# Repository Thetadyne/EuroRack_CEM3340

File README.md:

# SynthMeetupVCO-1
This repository is to hold assets (e.g., design files, code, datasheets) for the first VCO project of the Freeside Atlanta Synth Meetup.

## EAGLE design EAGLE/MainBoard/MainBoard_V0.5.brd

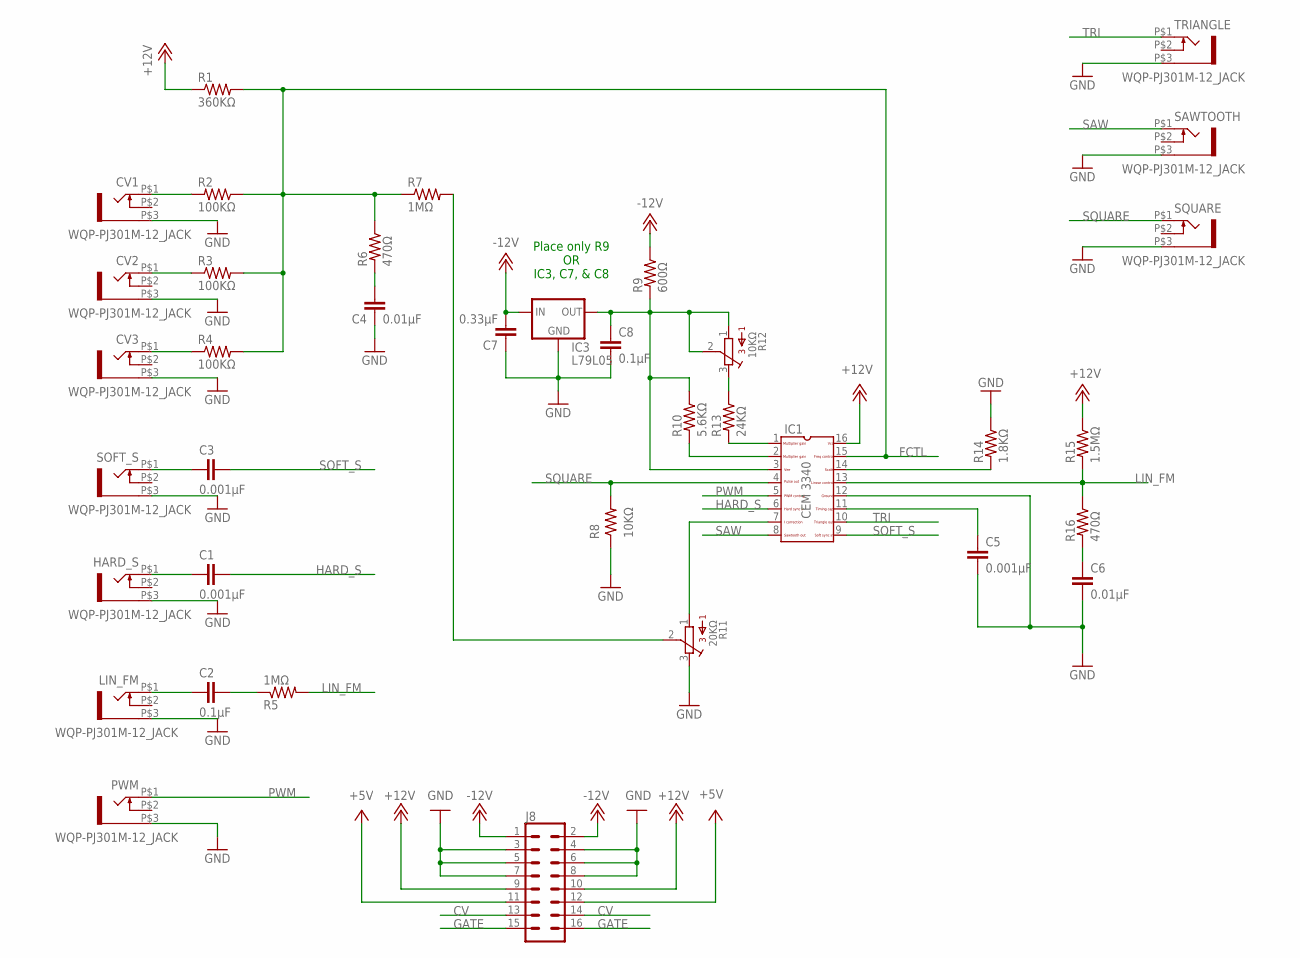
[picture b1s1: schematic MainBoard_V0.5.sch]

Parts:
C1, C3, C5: 0.001μF; C050-025X075
C2, C8: 0.1μF; C050-025X075
C4, C6: 0.01μF; C050-025X075
C7: 0.33μF; C050-025X075
CV1, CV2, CV3: WQP-PJ301M-12_JACK
HARD_S: WQP-PJ301M-12_JACK
IC1: CEM3340; DIL16
IC3: L79L05; TO-92
J8: CONN_08X2_SHROUD; 2X8-SHROUDED_LOCK
LIN_FM: WQP-PJ301M-12_JACK
PWM: WQP-PJ301M-12_JACK
R1: 360KΩ; 0207/10
R2, R3, R4: 100KΩ; 0207/10
R5, R7: 1MΩ; 0207/10
R6, R16: 470Ω; 0207/10
R8: 10KΩ; 0207/10
R9: 600Ω; 0207/10
R10: 5.6KΩ; 0207/10
R11: 20KΩ; 3386W
R12: 10KΩ; 3386W
R13: 24KΩ; 0207/10
R14: 1.8KΩ; 0207/10
R15: 1.5MΩ; 0207/10
SAWTOOTH: WQP-PJ301M-12_JACK
SOFT_S: WQP-PJ301M-12_JACK
SQUARE: WQP-PJ301M-12_JACK
TRIANGLE: WQP-PJ301M-12_JACK

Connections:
+5V: J8.11, J8.12
+12V: IC1.16, J8.9, J8.10, R1.1, R15.1
-12V: C7.2, IC3.2 (IN), J8.1, J8.2, R9.1
CV: J8.13, J8.14
FCTL: IC1.15, R1.2, R2.1, R3.2, R4.2, R6.1, R7.1
GATE: J8.15, J8.16
GND: C4.2, C5.2, C6.2, C7.1, C8.2, CV1.P$3 (1), CV2.P$3 (1), CV3.P$3 (1), HARD_S.P$3 (1), IC1.12, IC3.1 (GND), J8.3, J8.4, J8.5, J8.6, J8.7, J8.8, LIN_FM.P$3 (1), PWM.P$3 (1), R8.1, R11.3, R14.1, SAWTOOTH.P$3 (1), SOFT_S.P$3 (1), SQUARE.P$3 (1), TRIANGLE.P$3 (1)
HARD_S: C1.2, IC1.6
LIN_FM: IC1.13, R5.2, R15.2, R16.1
unnamed: IC1.2, R10.2
unnamed: C4.1, R6.2
unnamed: IC1.14, R14.2
unnamed: C2.1, LIN_FM.P$1 (2)
unnamed: C2.2, R5.1
unnamed: C6.1, R16.2
unnamed: C5.1, IC1.11
unnamed: IC1.1, R13.2
unnamed: R7.2, R11.2
unnamed: R12.3, R13.1
unnamed: IC1.7, R11.1
unnamed: CV1.P$1 (2), R2.2
unnamed: C8.1, IC1.3, IC3.3 (OUT), R9.2, R10.1, R12.1, R12.2
unnamed: C1.1, HARD_S.P$1 (2)
unnamed: CV2.P$1 (2), R3.1
unnamed: CV3.P$1 (2), R4.1
unnamed: C3.2, SOFT_S.P$1 (2)
PWM: IC1.5, PWM.P$1 (2)
SAW: IC1.8, SAWTOOTH.P$1 (2)
SOFT_S: C3.1, IC1.9
SQUARE: IC1.4, R8.2, SQUARE.P$1 (2)
TRI: IC1.10, TRIANGLE.P$1 (2)

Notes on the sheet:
Place only R9 OR IC3, C7, & C8

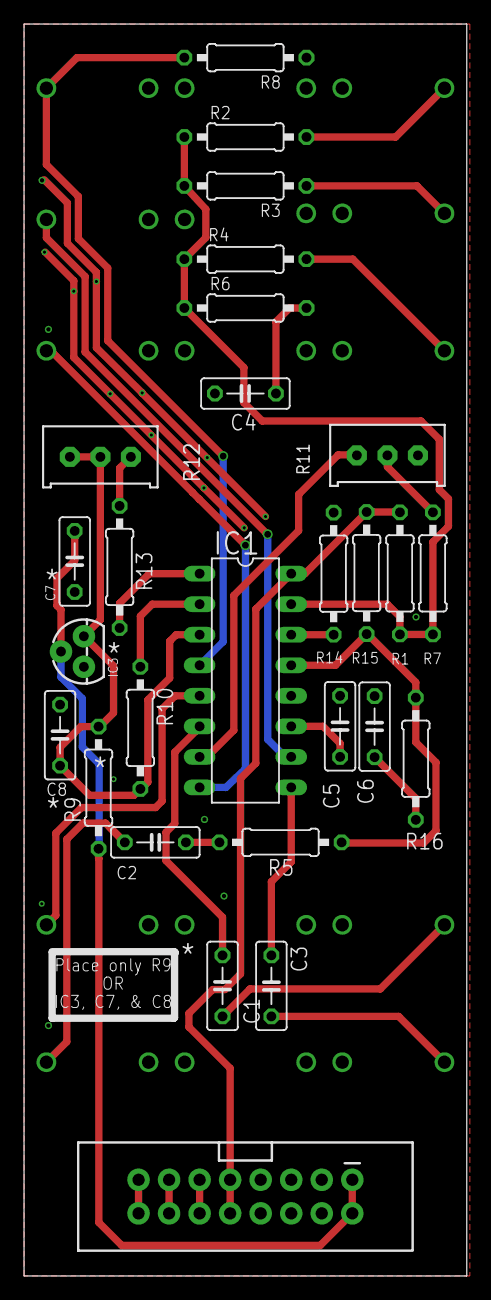
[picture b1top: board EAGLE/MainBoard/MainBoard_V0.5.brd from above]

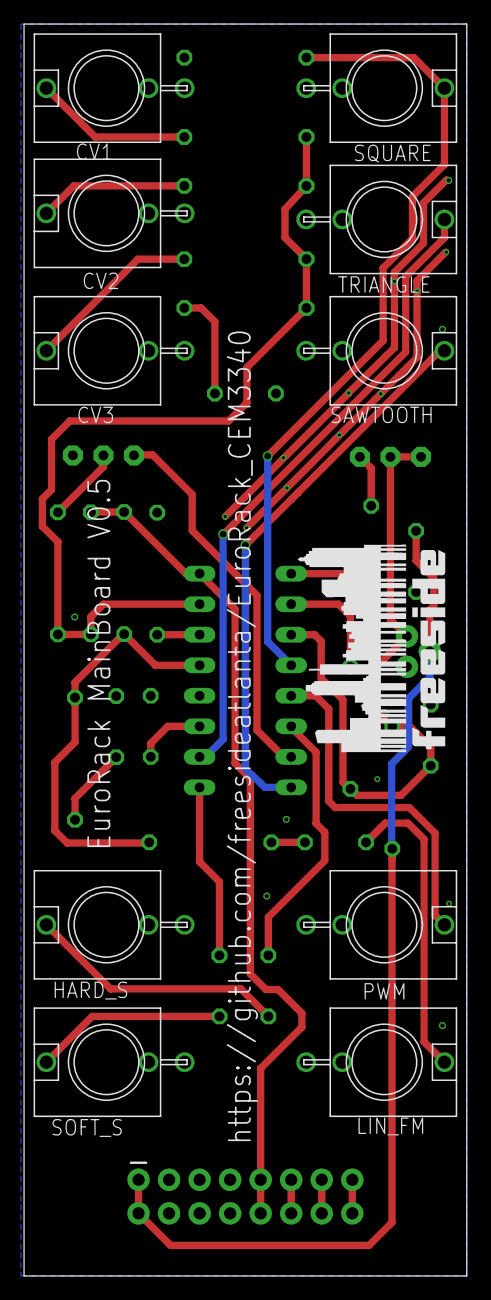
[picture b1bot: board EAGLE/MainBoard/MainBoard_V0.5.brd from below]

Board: 2 copper layers, 36.8 x 104.1 mm, 37 parts (10 on the bottom side), 31 nets.

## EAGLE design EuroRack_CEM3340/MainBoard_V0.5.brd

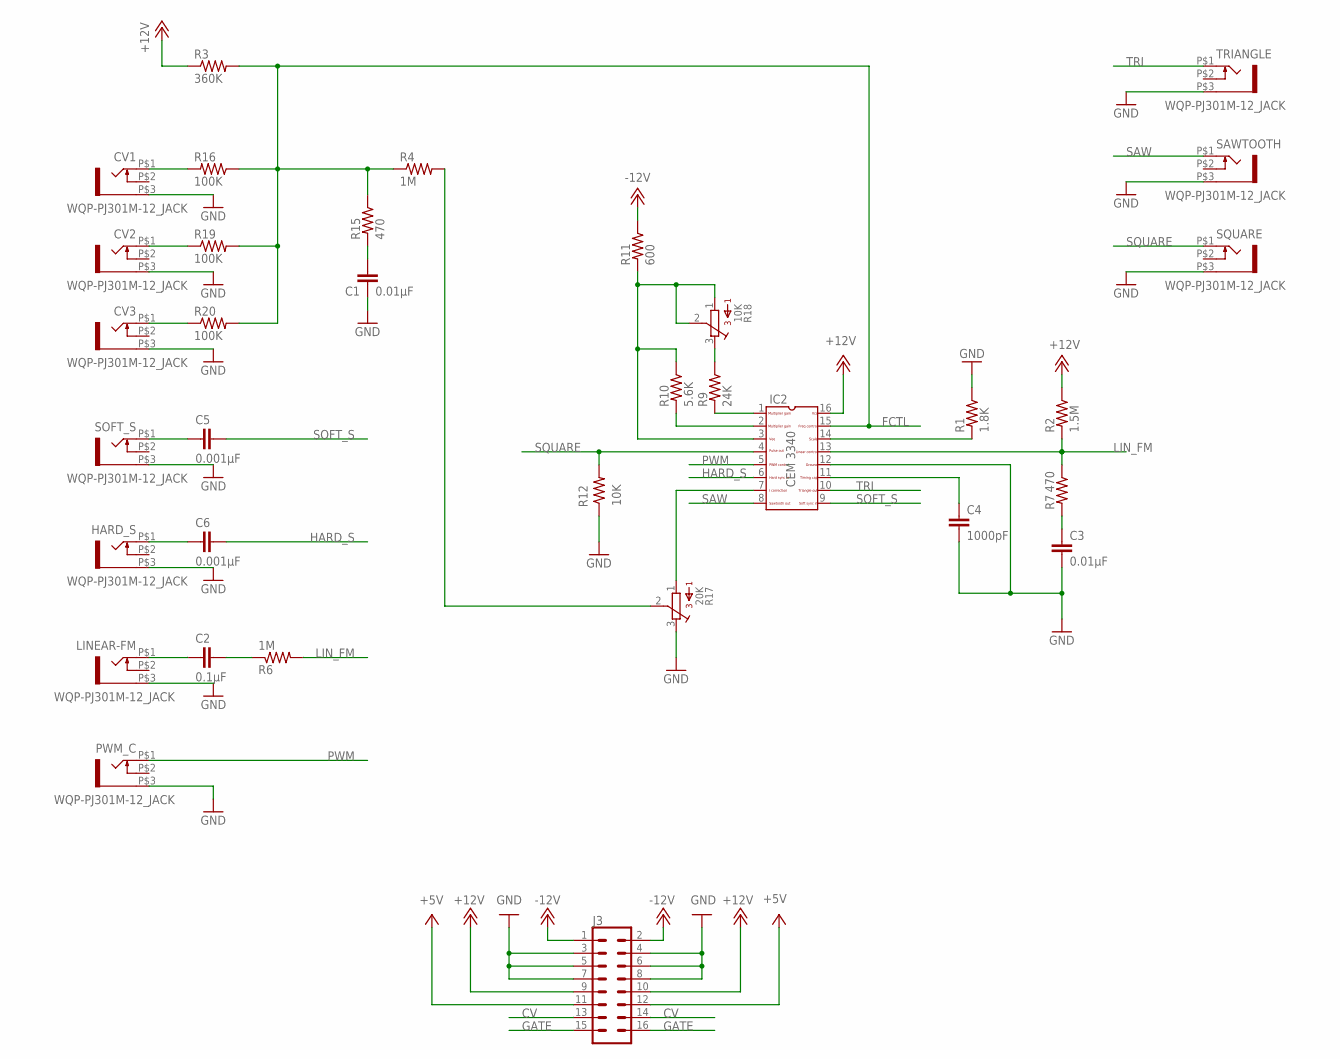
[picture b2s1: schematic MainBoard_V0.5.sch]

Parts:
C1, C3: 0.01μF; C050-025X075
C2: 0.1μF; C050-025X075
C4: 1000pF; C050-025X075
C5, C6: 0.001μF; C050-025X075
CV1, CV2, CV3: WQP-PJ301M-12_JACK
HARD_S: WQP-PJ301M-12_JACK
IC2: CEM3340; DIL16
J3: CONN_08X2_SHROUD; 2X8-SHROUDED_LOCK
LINEAR-FM: WQP-PJ301M-12_JACK
PWM_C: WQP-PJ301M-12_JACK
R1: 1.8K; 0207/10
R2: 1.5M; 0207/10
R3: 360K; 0207/10
R4, R6: 1M; 0207/10
R7, R15: 470; 0207/10
R9: 24K; 0207/10
R10: 5.6K; 0207/10
R11: 600; 0207/10
R12: 10K; 0207/10
R16, R19, R20: 100K; 0207/10
R17: 20K; 3386W
R18: 10K; 3386W
SAWTOOTH: WQP-PJ301M-12_JACK
SOFT_S: WQP-PJ301M-12_JACK
SQUARE: WQP-PJ301M-12_JACK
TRIANGLE: WQP-PJ301M-12_JACK

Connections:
+5V: J3.11, J3.12
+12V: IC2.16, J3.9, J3.10, R2.1, R3.1
-12V: J3.1, J3.2, R11.1
CV: J3.13, J3.14
FCTL: IC2.15, R3.2, R4.1, R15.1, R16.1, R19.2, R20.2
GATE: J3.15, J3.16
GND: C1.2, C3.2, C4.2, CV1.P$3 (1), CV2.P$3 (1), CV3.P$3 (1), HARD_S.P$3 (1), IC2.12, J3.3, J3.4, J3.5, J3.6, J3.7, J3.8, LINEAR-FM.P$3 (1), PWM_C.P$3 (1), R1.1, R12.1, R17.3, SAWTOOTH.P$3 (1), SOFT_S.P$3 (1), SQUARE.P$3 (1), TRIANGLE.P$3 (1)
HARD_S: C6.2, IC2.6
LIN_FM: IC2.13, R2.2, R6.2, R7.1
unnamed: IC2.2, R10.2
unnamed: C1.1, R15.2
unnamed: IC2.14, R1.2
unnamed: C2.1, LINEAR-FM.P$1 (2)
unnamed: C2.2, R6.1
unnamed: C3.1, R7.2
unnamed: C4.1, IC2.11
unnamed: IC2.1, R9.2
unnamed: R4.2, R17.2
unnamed: R9.1, R18.3
unnamed: IC2.7, R17.1
unnamed: CV1.P$1 (2), R16.2
unnamed: IC2.3, R10.1, R11.2, R18.1, R18.2
unnamed: C6.1, HARD_S.P$1 (2)
unnamed: CV2.P$1 (2), R19.1
unnamed: CV3.P$1 (2), R20.1
unnamed: C5.2, SOFT_S.P$1 (2)
PWM: IC2.5, PWM_C.P$1 (2)
SAW: IC2.8, SAWTOOTH.P$1 (2)
SOFT_S: C5.1, IC2.9
SQUARE: IC2.4, R12.2, SQUARE.P$1 (2)
TRI: IC2.10, TRIANGLE.P$1 (2)

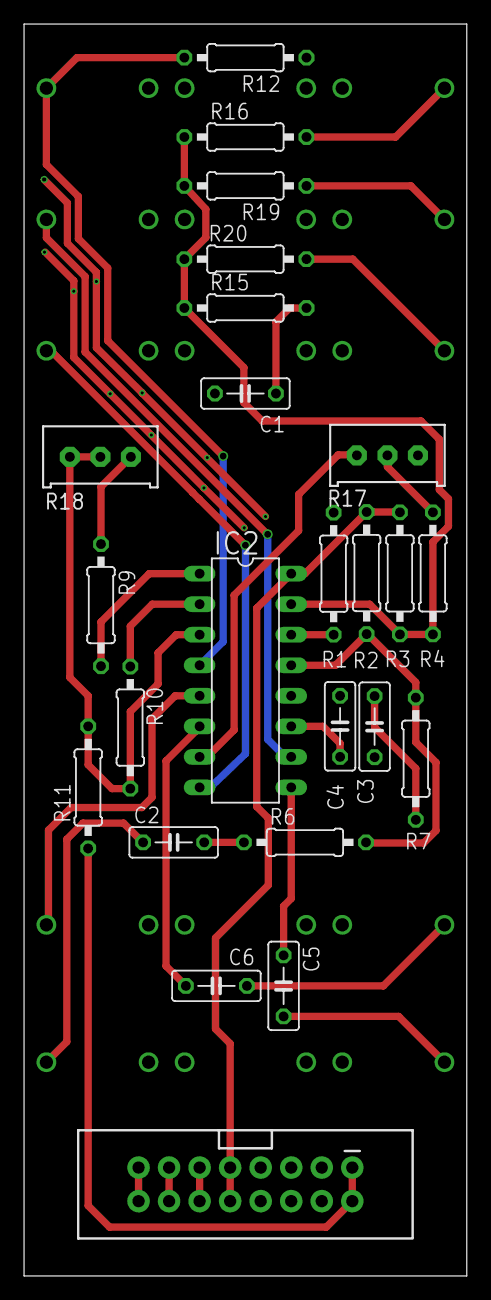
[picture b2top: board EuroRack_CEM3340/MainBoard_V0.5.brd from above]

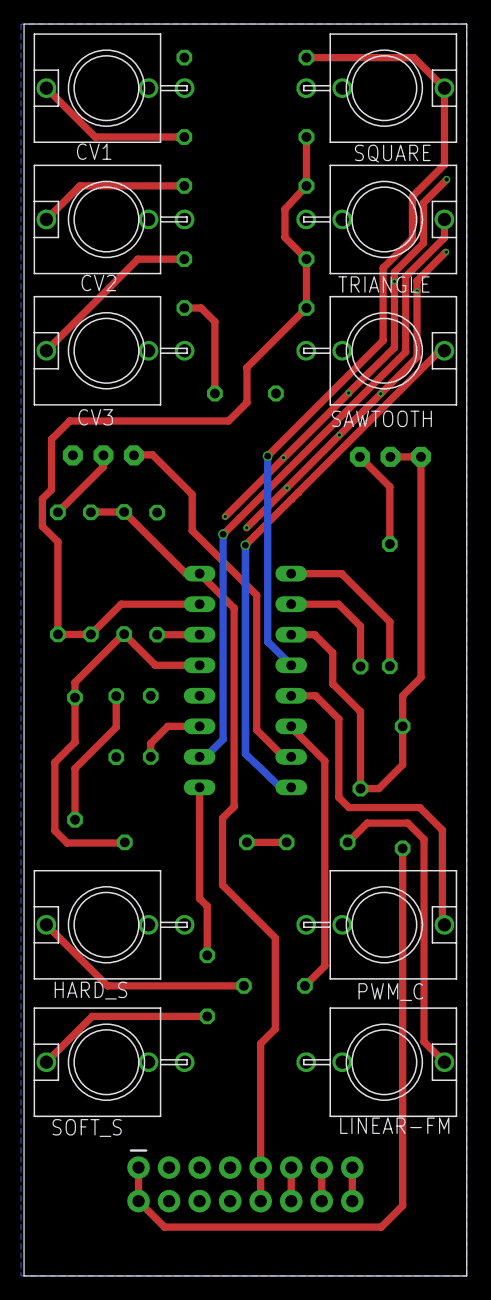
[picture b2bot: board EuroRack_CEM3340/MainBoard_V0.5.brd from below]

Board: 2 copper layers, 36.8 x 104.1 mm, 34 parts (10 on the bottom side), 31 nets.

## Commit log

2019-01-20 Added Eagle Gitignore
2019-01-20 Directory Resturcture
2019-01-20 Fix Gitignore to include eagle project file
2019-01-20 Actually Remove Eagle.epf
2019-01-20 Renumber Parts
2019-01-23 Logo, Top Ground Planes
2019-01-23 Minor Silk Update
2019-01-23 Add 5V Reg. CAM Files
2019-02-07 Update Power IC Add Optional Component Clarification
2019-02-07 Version Update to 0.6
2019-03-18 Added parts list.

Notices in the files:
parts and their libraries:
SparkFun-Connectors: Licensing: Creative Commons ShareAlike 4.0 International - https://creativecommons.org/licenses/by-sa/4.0
